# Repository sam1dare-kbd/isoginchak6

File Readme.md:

# isoginchak6

## What is isoginchak6?

ISOエンターを使った6キーのマクロパッドです。
Isoginckak6 is a 6-key macro pad with ISO enter.

<br>
<br>

## Build Guide  
https://note.com/sam1dare/n/nc1cb8ba09af6
(Japanese text only.)  

<br>

## License  
このプロジェクトは MITライセンスに基づいてライセンスされています。詳細については、LICENSE.txt ファイルを参照してください。  
This project is licensed under the MIT License, see the LICENSE.txt file for details.

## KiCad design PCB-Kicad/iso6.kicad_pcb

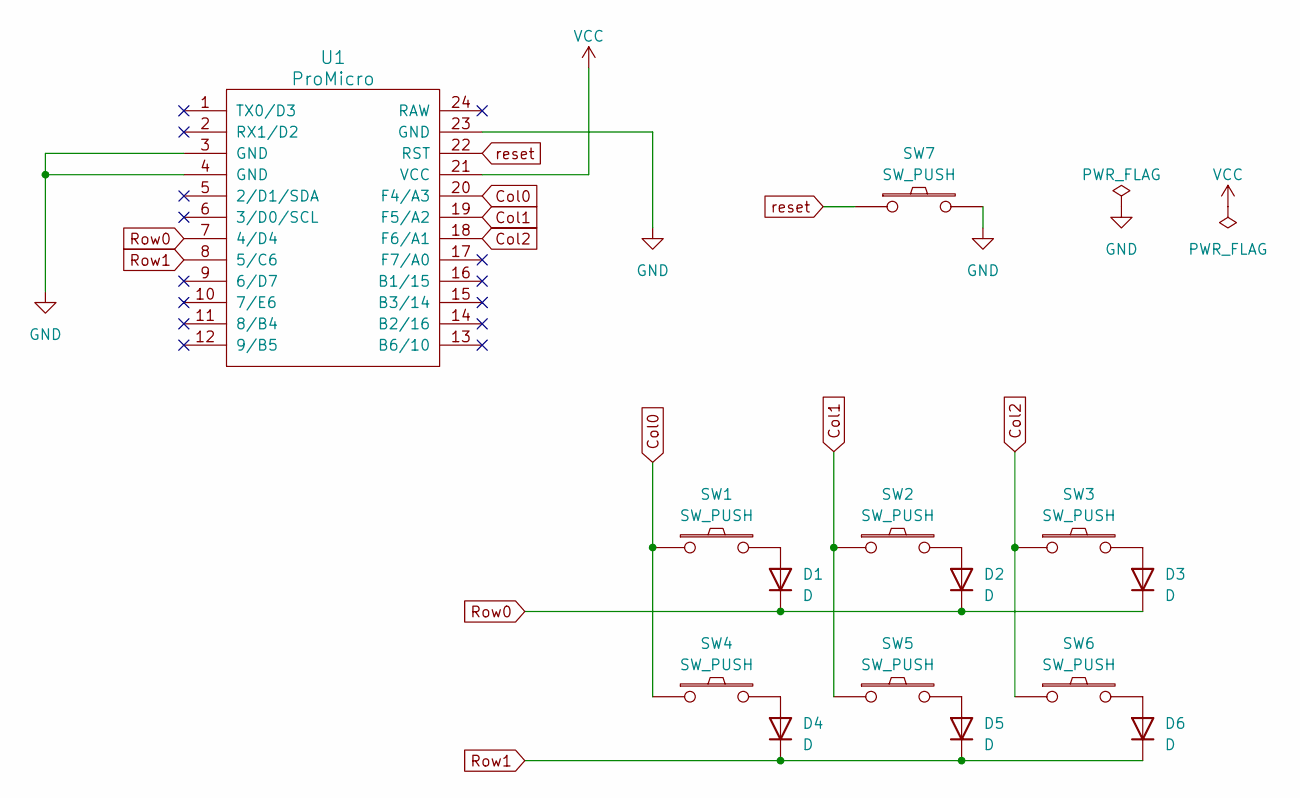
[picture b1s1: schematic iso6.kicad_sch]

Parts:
D1, D2, D3, D4, D5, D6: D; Diode_TH_SMD
SW1, SW2, SW3: SW_PUSH; CherryMX_Solder_1u
SW4: SW_PUSH; CherryMX_Solder_1.5u
SW5: SW_PUSH; CherryMX_Solder_1.75u
SW6: SW_PUSH; SW_Cherry_MX_ISOEnter_PCB
SW7: SW_PUSH; ResetSW
U1: ProMicro; ProMicro_v2_1side

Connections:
Col0: SW1.1, SW4.1, U1.20 (F4/A3)
Col1: SW2.1, SW5.1, U1.19 (F5/A2)
Col2: SW3.1, SW6.1, U1.18 (F6/A1)
GND: SW7.2, U1.3 (GND), U1.4 (GND), U1.23 (GND)
unnamed: D1.2 (A), SW1.2
unnamed: D2.2 (A), SW2.2
unnamed: D3.2 (A), SW3.2
unnamed: D4.2 (A), SW4.2
unnamed: D5.2 (A), SW5.2
unnamed: D6.2 (A), SW6.2
Row0: D1.1 (K), D2.1 (K), D3.1 (K), U1.7 (4/D4)
Row1: D4.1 (K), D5.1 (K), D6.1 (K), U1.8 (5/C6)
VCC: U1.21 (VCC)
reset: SW7.1, U1.22 (RST)

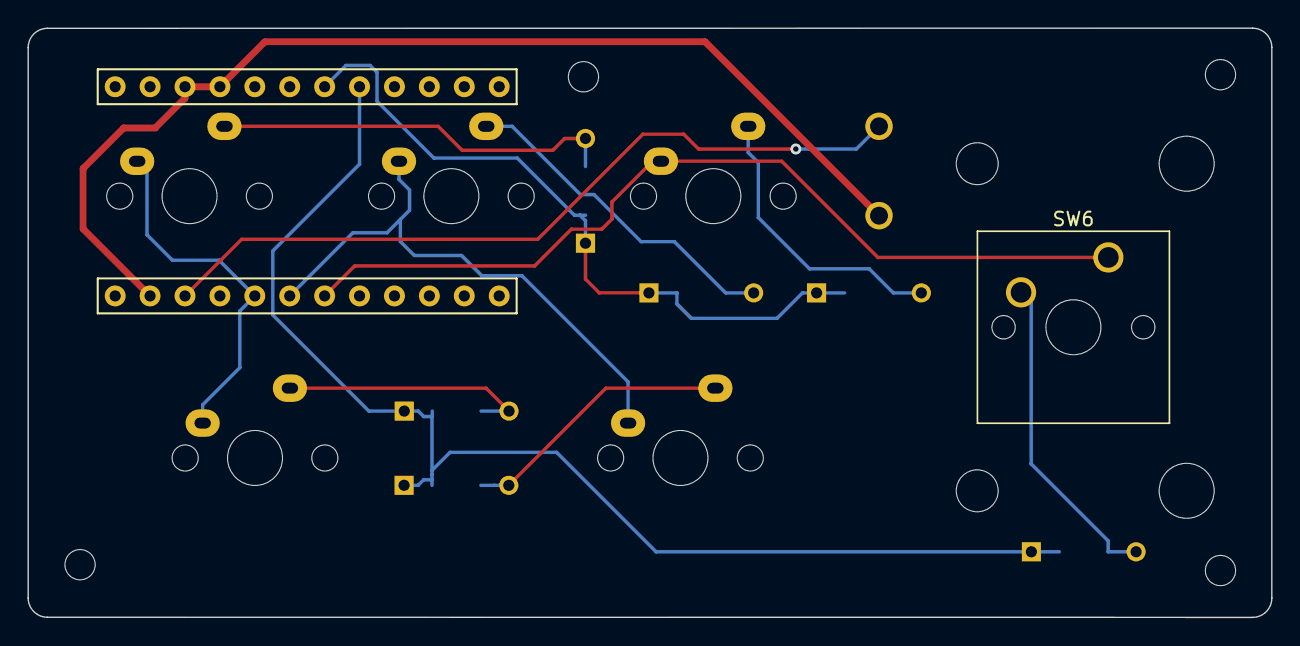
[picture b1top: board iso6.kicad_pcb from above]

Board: 2 copper layers, 90.5 x 42.9 mm, 19 parts (1 on the bottom side), 13 nets.

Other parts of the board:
00: LOGO; sam1dare_logo
Ref00, Ref01, Ref02, Ref03: Val**; m2_Screw_Hole

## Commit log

2023-09-21 Create LICENSE
2024-09-05 Update LICENSE
